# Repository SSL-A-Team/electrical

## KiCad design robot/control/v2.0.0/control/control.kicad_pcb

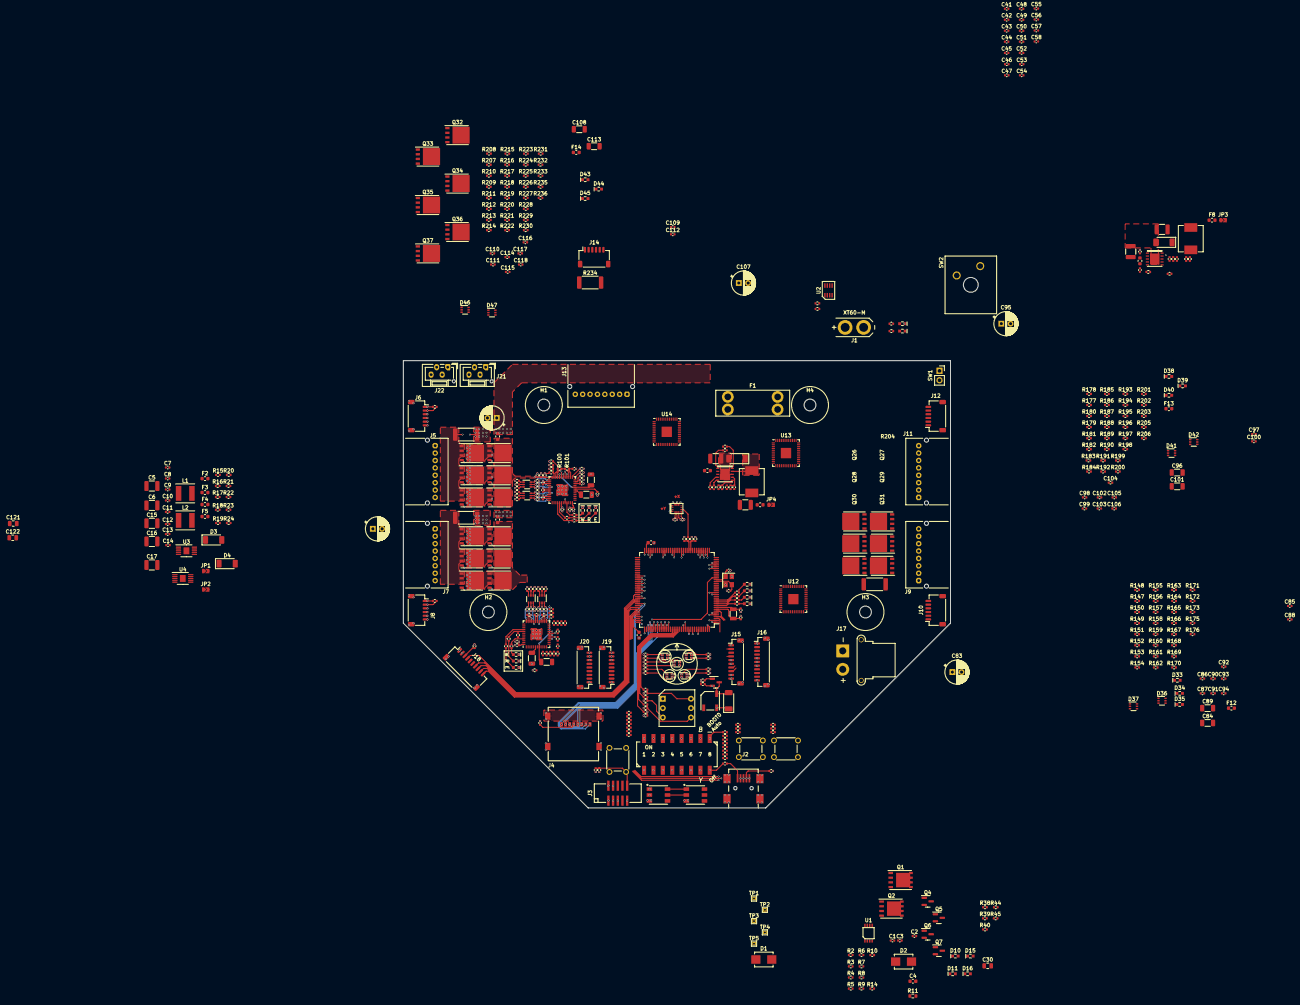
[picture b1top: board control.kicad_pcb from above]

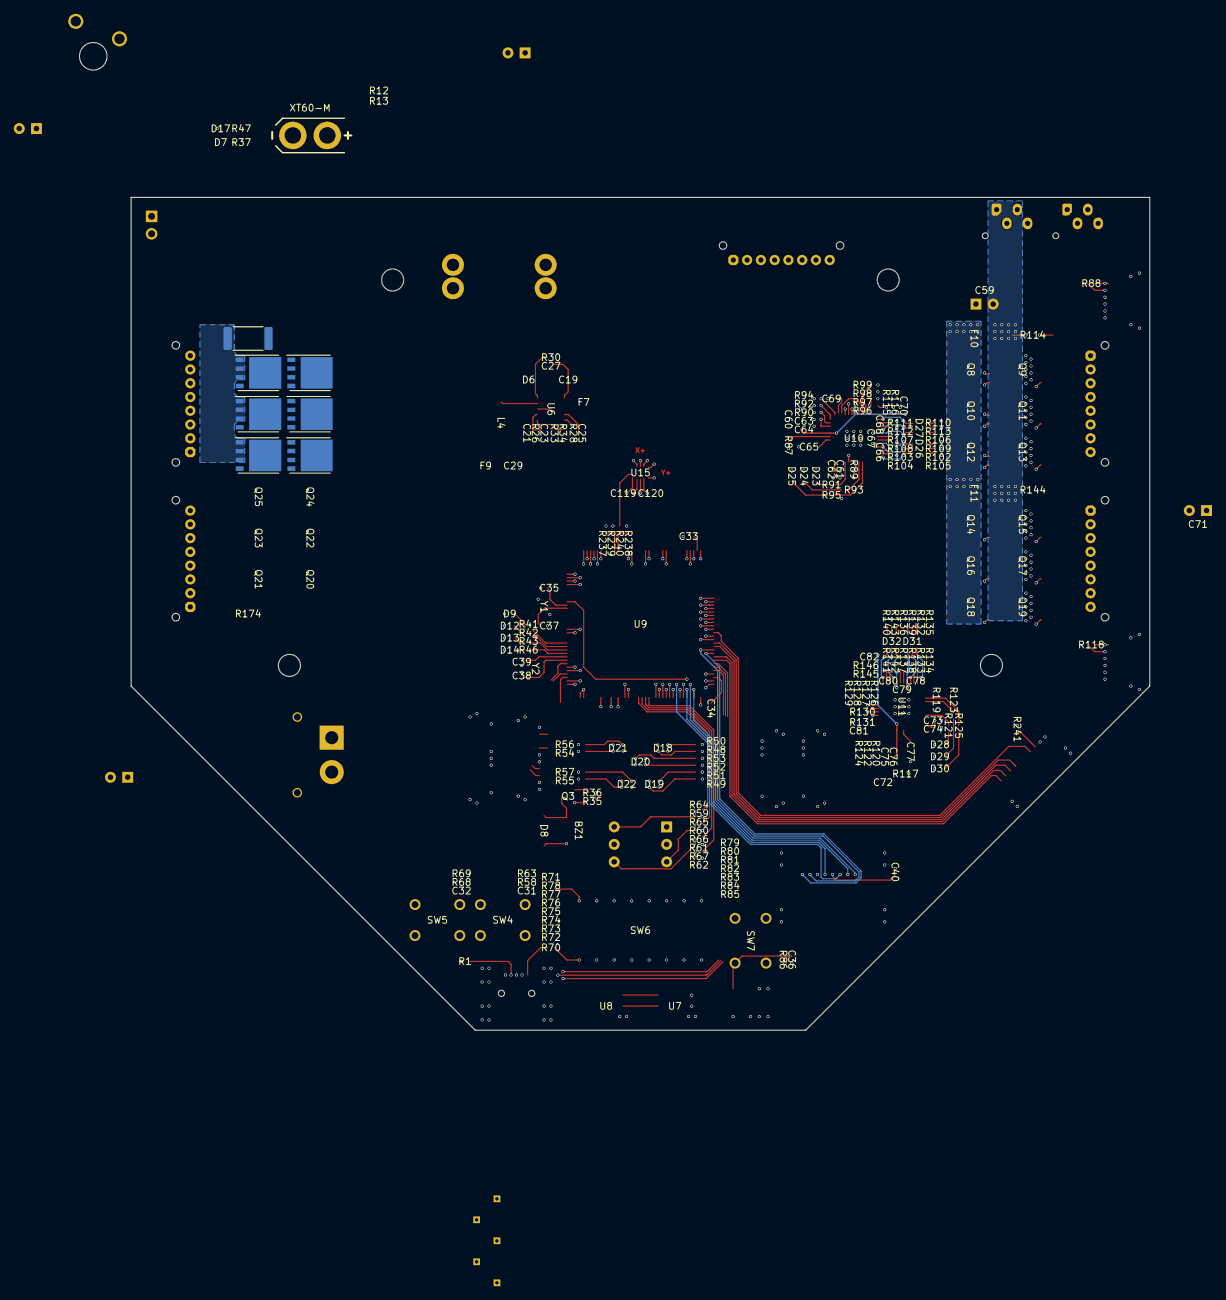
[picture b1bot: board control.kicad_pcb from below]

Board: 6 copper layers, 148.0 x 121.0 mm, 525 parts (7 on the bottom side), 435 nets.

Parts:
BZ1: MLT-5020
C1, C2, C3, C13, C14, C26, C27, C31, C32, C36, C40, C41, C42, C43, C44, C45, C46, C47, C48, C49, C50, C51, C53, C56, C57, C58, C62, C64, C66, C67, C68, C74, C76, C78, C79, C80, C86, C88, C90, C91, C92, C98, C100, C102, C103, C104, C110, C112, C114, C115, C116, C119, C120: 0.1uF 63V; C_0402_1005Metric
C4: 4700pF 63V; C_0603_1608Metric
C5, C6, C18, C19: 4.7uF 63V; C_1210_3225Metric
C7: 36pF; C_0402_1005Metric
C8: 24pF; C_0402_1005Metric
C9: 2700pF; C_0402_1005Metric
C10: 2200pF; C_0402_1005Metric
C11, C12: 10000pF; C_0402_1005Metric
C15, C16, C17: 100uF 10V; C_1210_3225Metric
C20, C21: 6.8pF; C_0402_1005Metric
C22, C23: 560pF; C_0402_1005Metric
C24, C25: 8200pF; C_0402_1005Metric
C28, C29: 47uF 25V; C_1210_3225Metric
C30, C121, C122: 4.7uF 25V; C_0805_2012Metric
C33, C34: 2.2uF 10V; C_0603_1608Metric
C35, C37: 11pF; C_0402_1005Metric
C38, C39: 8pF; C_0402_1005Metric
C52, C54, C55, C61, C63, C69, C70, C73, C75, C81, C82, C85, C87, C93, C94, C97, C99, C105, C106, C109, C111, C117, C118: 1uF 10V; C_0402_1005Metric
C59, C71, C83, C95, C107: 63ZLH47MEFC6.3X11; CP_Radial_D6.3mm_H11.0mm_P2.50mm
C60, C65, C72, C77, C84, C89, C96, C101, C108, C113: 1uF 63V; C_1206_3216Metric
D1, D2: 824521261; D_SMB_Non-Polar
D3, D4, D5, D6, D8: RBR5LAM60ATR; D_SOD-128
D7: XL-1608UWC-04; LED0603
D9, D12, D13, D14, D24, D29, D34, D39, D44: XL-1608UGC-04; LED0603
D10, D11, D15, D16, D25, D30, D35, D40, D45: XL-1608SURC-06; LED0603
D17, D23, D28, D33, D38, D43: XL-1608UOC-06; LED0603
D18, D19, D21, D22: LTST-C195KGJRKT; LED0606_S_1324
D20: MHT194YBCT; LED0606_Z_1324
D26, D27, D31, D32, D36, D37, D41, D42, D46, D47: BAS16VY; SOT-363_SC-70-6
F1: 15A; 3557-2
F2, F3, F4, F5, F6, F7: 0467002.NRHF; Fuse_0603_1608Metric
F8, F9: 0467004.NRHF; Fuse_0603_1608Metric
F10, F11, F12, F13, F14: 0467003.NRHF; Fuse_0603_1608Metric
H1, H2, H3, H4: M3; MountingHole_3.2mm_M3
J1: EC3-M; XT60-M_TH_WireMount
J2: 10033527-N3112MLF
J3: ARM_SWD; 3221-10-0300-00
J4: MEM2067-02-180-00-A
J5, J7, J9, J11, J13: S08B-PASK-2; JST_PA_S08B-PASK-2_1x08_P2.00mm_Horizontal
J6, J8, J10, J12, J14: SM06B-SRSS-TB; JST_SH_SM06B-SRSS-TB_1x06-1MP_P1.00mm_Horizontal
J15: BM10B-SRSS-TB; JST_SH_BM10B-SRSS-TB_1x10-1MP_P1.00mm_Vertical
J16: BM11B-SRSS-TB; JST_SH_BM11B-SRSS-TB_1x11-1MP_P1.00mm_Vertical
J17: XT30PW-F; AMASS_XT30PW-F_1x02_P2.50mm_Horizontal
J18: SM10B-SRSS-TB; JST_SH_SM10B-SRSS-TB_1x10-1MP_P1.00mm_Horizontal
J19, J20: BM09B-SRSS-TB; JST_SH_BM09B-SRSS-TB_1x09-1MP_P1.00mm_Vertical
J21, J22: B04B-ZESK-1D; JST_ZE_B04B-ZESK-1D_1x04_P1.50mm_Vertical
JP1: SB_{+3.3V}; SolderJumper-2_2.0x1.2mm_Closed
JP2: SB_{+5V}; SolderJumper-2_2.0x1.2mm_Closed
JP3: SB_{+12V}; SolderJumper-2_2.0x1.2mm_Closed
JP4: SB_{FAN}; SolderJumper-2_2.0x1.2mm_Closed
L1, L2: SDEI054T-100MS; SDEI054T
L3, L4: 0630CDMCCDS-4R7MC; 0630CDMCCDS
Q1, Q2: SQJA80EP-T1_GE3; PowerPAK_SO-8L_Single
Q3, Q4, Q5, Q6, Q7: BSS138K; SOT-23
Q8, Q9, Q10, Q11, Q12, Q13, Q14, Q15, Q16, Q17, Q18, Q19, Q20, Q21, Q22, Q23, Q24, Q25, Q26, Q27, Q28, Q29, Q30, Q31, Q32, Q33, Q34, Q35, Q36, Q37: STL90N10F7; PowerFLAT_5x6
R1, R12, R13, R14, R19, R20, R29, R30, R35, R38, R58, R59, R60, R61, R62, R68, R72, R73, R74, R75, R76, R77, R78, R86, R87, R88, R89, R90, R92, R94, R117, R118, R119, R120, R122, R124, R147, R148, R149, R150, R152, R154, R177, R178, R179, R180, R182, R184, R207, R208, R209, R210, R212, R214, R237, R238, R241: 4.7k; R_0402_1005Metric
R2, R7: 1k; R_0402_1005Metric
R3: 10M; R_0402_1005Metric
R4: 1.5M; R_0402_1005Metric
R5: 69.8k; R_0402_1005Metric
R6: 232k; R_0402_1005Metric
R8, R9, R36, R102, R105, R106, R109, R110, R113, R132, R135, R136, R139, R140, R143, R162, R165, R166, R169, R170, R173, R192, R195, R196, R199, R200, R203, R222, R225, R226, R229, R230, R233: 10; R_0402_1005Metric
R10: 100k; R_0402_1005Metric
R11: 5.1k; R_0603_1608Metric
R15: 18.7k; R_0402_1005Metric
R16, R37: 23.7k; R_0402_1005Metric
R17, R18: 162k; R_0402_1005Metric
R21: 30.9k; R_0402_1005Metric
R22, R24, R32, R34, R39, R40, R41, R42, R43, R44, R45, R46, R47, R48, R49, R50, R51, R52, R53, R54, R55, R56, R57, R70, R91, R93, R95, R99, R121, R123, R125, R129, R151, R153, R155, R159, R181, R183, R185, R189, R211, R213, R215, R219: 10k; R_0402_1005Metric
R23: 52.3k; R_0402_1005Metric
R25, R26: 56.2k; R_0402_1005Metric
R27, R28: 61.9k; R_0402_1005Metric
R31, R33: 140k; R_0402_1005Metric
R63, R64, R65, R66, R67, R69, R79, R80, R81, R82, R83, R84, R85, R239, R240: 100; R_0402_1005Metric
R71: 16k; R_0402_1005Metric
R96, R115, R126, R145, R156, R175, R186, R205, R216, R235: 2.37k; R_0402_1005Metric
R97, R127, R157, R187, R217: 649k; R_0402_1005Metric
R98, R128, R158, R188, R218: 53.6k; R_0402_1005Metric
R100, R130, R160, R190, R220: 26.7k; R_0402_1005Metric
R101, R131, R161, R191, R221: 22; R_0402_1005Metric
R103, R104, R107, R108, R111, R112, R133, R134, R137, R138, R141, R142, R163, R164, R167, R168, R171, R172, R193, R194, R197, R198, R201, R202, R223, R224, R227, R228, R231, R232: 62; R_0402_1005Metric
R114, R144, R174, R204, R234: HoLLR2512-3W-62mR-1%; R_2512_6332Metric
R116, R146, R176, R206, R236: 143k; R_0402_1005Metric
SW1: HDR_2P; PinSocket_1x02_P2.54mm_Vertical
SW2: CPG151101D91; SW_Kailh_PG1511
SW3: 221ADC16
SW4, SW5, SW7: TS02-66-73-BK-160-SCR-D
SW6: 219-8MST
TP1: Main; TestPoint_THTPad_1.0x1.0mm_Drill0.5mm
TP2: +3.3V; TestPoint_THTPad_1.0x1.0mm_Drill0.5mm
TP3: +5V; TestPoint_THTPad_1.0x1.0mm_Drill0.5mm
TP4: +12V; TestPoint_THTPad_1.0x1.0mm_Drill0.5mm
TP5: +V_{FAN}; TestPoint_THTPad_1.0x1.0mm_Drill0.5mm
U1: LTC4367; MS8
U2: LTC2955-1; LTC2955-TS8
U3, U4: TPS54260DGQ; HVSSOP-10-1EP_3x3mm_P0.5mm_EP1.57x1.88mm
U5, U6: TPS54561DPR; DPR
U7, U8: SK9822
U9: STM32H723ZGT6; LQFP-144_20x20mm_P0.5mm
U10, U11, U12, U13, U14: STSPIN32F0B; QFN-48-1EP_7x7mm_P0.5mm_EP2.8x2.8mm
U15: BMI323
Y1: TAXM8M4RDBCCT2T; Crystal_SMD_3225-4Pin_3.2x2.5mm
Y2: QT3CD-32.768KEZC-T; Crystal_SMD_3215-2Pin_3.2x1.5mm

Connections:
+3.3V: BZ1.1 (-), C40.1, C41.1, C42.1, C43.1, C44.1, C45.1, C46.1, C47.1, C48.1, C49.1, C50.1, C51.1, C52.1, C53.1, C54.1, C55.1, C56.1, C57.1, C58.1, C61.1, C62.1, C63.1, C64.1, C73.1, C74.1, C75.1, C76.1, C85.1, C86.1, C87.1, C88.1, C97.1, C98.1, C99.1, C100.1, C109.1, C110.1, C111.1, C112.1, C119.1, C120.1, D8.1 (K), J3.1 (VTref), J4.4 (VDD), J5.1, J6.1, J7.1, J8.1, J9.1, J10.1, J11.1, J12.1, J13.1, J14.1, J15.9, J16.11, J18.2, J19.7, J20.7, JP1.2 (B), R1.1, R12.1, R13.1, R19.1, R20.1, R29.1, R30.1, R50.2, R51.2, R53.2, R56.2, R57.2, R58.2, R68.2, R86.1, R88.2, R90.1, R92.1, R94.1, R97.1, R116.1, R118.2, R120.1, R122.1, R124.1, R127.1, R146.1, R148.2, R150.1, R152.1, R154.1, R157.1, R176.1, R178.2, R180.1, R182.1, R184.1, R187.1, R206.1, R208.2, R210.1, R212.1, R214.1, R217.1, R236.1, R237.1, R238.1, R241.1, SW3.C, SW6.1, SW6.2, SW6.3, SW6.4, SW6.5, SW6.6, SW6.7, TP2.1, U9.6 (VBAT), U9.17 (VDD), U9.30 (VDD), U9.32 (VREF+), U9.33 (VDDA), U9.39 (VDD), U9.52 (VDD), U9.62 (VDD), U9.72 (VDD), U9.84 (VDD), U9.95 (VDD33USB), U9.108 (VDD), U9.121 (VDD), U9.131 (VDD), U9.143 (PDR_ON), U9.144 (VDD), U10.10 (VDDA), U10.48 (VDD), U11.10 (VDDA), U11.48 (VDD), U12.10 (VDDA), U12.48 (VDD), U13.10 (VDDA), U13.48 (VDD), U14.10 (VDDA), U14.48 (VDD), U15.5 (VDDIO), U15.8 (VDD)
+5V: C30.2, J15.10, J19.8, J20.8, JP2.2 (B), TP3.1, U7.4 (VCC), U8.4 (VCC)
+12V: J19.9, J20.9, JP3.2 (B), TP4.1
+V_{BATT(FUSED)}: D1.2 (A2), F1.2, Q1.5 (D), R2.2, R3.1
+V_{BATT(PROTECTED)}: C59.1, C71.1, C83.1, C95.1, C107.1, F2.2, F3.2, F6.2, F7.2, F10.1, F11.1, F12.1, F13.1, F14.1, J17.2, Q2.5 (D), R10.1, R14.1, R37.1, R39.1, R40.1, R44.1, R45.1, TP1.1, U1.7 (V_{OUT})
+V_{BATT(RAW)}: F1.1, J1.2
+V_{FAN}: C121.2, C122.2, J21.2, J22.2, JP4.2 (B), TP5.1
/AIRDRIBBLER.PWM1: J21.4, U9.50 (PF12)
/AIRDRIBBLER.PWM2: J22.4, U9.53 (PF13)
/EXTLOGIC.CK: J19.4, U9.79 (PD10)
/EXTLOGIC.NSS: J19.3, U9.80 (PD11)
/EXTLOGIC.RX: J19.5, U9.70 (PB11)
/EXTLOGIC.TX: J19.6, U9.69 (PB10)
/EXTLOGIC.~DET: J19.2, U9.68 (PE15)
/FLOW.BOOT0: J20.4, U9.58 (PE7)
/FLOW.RX: J20.5, U9.56 (PG0)
/FLOW.TX: J20.6, U9.57 (PG1)
/FLOW.~DET: J20.2, U9.60 (PE9)
/FLOW.~RST: J20.3, U9.59 (PE8)
/IMU.INT1: J16.4, R237.2, R239.2, U9.47 (PB1)
/IMU.INT2: J16.3, R238.2, R240.2, U9.48 (PB2)
/IMU.MISO: J16.6, U9.42 (PA6), U15.1 (SDO)
/IMU.MOSI: J16.7, U9.43 (PA7), U15.14 (SDx)
/IMU.SCK: J16.5, U9.41 (PA5), U15.13 (SCx)
/IMU.~DET: J16.2, U9.49 (PF11)
/IMU.~SS0: U9.40 (PA4), U15.12 (CSB)
/IMU.~SS1: J16.10, U9.44 (PC4)
/IMU.~SS2: J16.9, U9.45 (PC5)
/IMU.~SS3: J16.8, U9.46 (PB0)
/Indicators/BUZZER: R35.1, R36.1, U9.5 (PE6)
/Indicators/DOTSTAR.CLK: R38.1, U7.2 (CKI), U9.133 (PB3/SWO/JTDO)
/Indicators/DOTSTAR.DAT: U7.1 (SDI), U9.135 (PB5)
/Indicators/LED.0: R41.1, U9.13 (PF3)
/Indicators/LED.1: R42.1, U9.12 (PF2)
/Indicators/LED.2: R43.1, U9.11 (PF1)
/Indicators/LED.3: R46.1, U9.10 (PF0)
/Indicators/PGOOD_{+5V}: Q6.1 (G), R20.2, U4.6 (PWRGD), U5.3 (EN), U6.3 (EN)
/Indicators/PGOOD_{+12V}: Q5.1 (G), R29.2, U5.10 (PWRGD)
/Indicators/PGOOD_{FAN}: Q7.1 (G), R30.2, U6.10 (PWRGD)
/Indicators/ROBOTID_{DISP}.BL: D19.2 (A2), D19.3 (K1), U9.115 (PD1)
/Indicators/ROBOTID_{DISP}.BR: D22.2 (A2), D22.3 (K1), U9.117 (PD3)
/Indicators/ROBOTID_{DISP}.FL: D18.2 (A2), D18.3 (K1), U9.114 (PD0)
/Indicators/ROBOTID_{DISP}.FR: D21.2 (A2), D21.3 (K1), U9.118 (PD4)
/Indicators/ROBOTID_{DISP}.TeamBlue: D20.2 (A2), D20.3 (K1), U9.85 (PD14)
/Indicators/ShutdownInitiated: R47.1, U9.14 (PF4)
/KICKER.BOOT0: J18.9, U9.100 (PA8)
/KICKER.PWRON: J18.4, U9.93 (PG8)
/KICKER.RX: J18.8, U9.97 (PC7)
/KICKER.TX: J18.7, U9.96 (PC6)
/KICKER.~DET: J18.3, R241.2
/KICKER.~RST: J18.10, U9.101 (PA9)
/Load Switch/PGOOD_{VBATT}: R10.2, U1.6 (~FAULT), U3.3 (EN)
/Load Switch/~INT_{PWRBTN}: R12.2, U2.8 (~INT), U9.55 (PF15)
/Load Switch/~KILL_{PWR}: R13.2, U2.2 (~KILL), U9.54 (PF14)
/MCU/BOOT0: R71.2, SW6.9, U9.138 (BOOT0)
/MCU/DIP.1: R79.2, U9.92 (PG7)
/MCU/DIP.2: R80.2, U9.91 (PG6)
/MCU/DIP.3: R81.2, U9.90 (PG5)
/MCU/DIP.4: R82.2, U9.89 (PG4)
/MCU/DIP.5: R83.2, U9.88 (PG3)
/MCU/DIP.6: R84.2, U9.87 (PG2)
/MCU/ID_{SW}.IDX0: R67.2, U9.124 (PG9)
/MCU/ID_{SW}.IDX1: R66.2, U9.125 (PG10)
/MCU/ID_{SW}.IDX2: R65.2, U9.126 (PG11)
/MCU/ID_{SW}.IDX3: R64.2, U9.127 (PG12)
/MCU/IsBlueTeam: R85.2, U9.86 (PD15)
/MCU/MOTOR_{BL}.BOOT0: R119.1, U9.20 (PF8), U11.42 (BOOT0)
/MCU/MOTOR_{BL}.RX: U9.18 (PF6), U11.38 (PA14/SWDCLK/USART1_{TX}/BL_UART_{TX})
/MCU/MOTOR_{BL}.TX: U9.19 (PF7), U11.39 (PA15/USART1_{RX}/BL_UART_{RX})
/MCU/MOTOR_{BL}.~RST: R117.2, U9.21 (PF9), U11.7 (NRST)
/MCU/MOTOR_{BR}.BOOT0: R149.1, U9.140 (PB9), U12.42 (BOOT0)
/MCU/MOTOR_{BR}.RX: U9.141 (PE0), U12.38 (PA14/SWDCLK/USART1_{TX}/BL_UART_{TX})
/MCU/MOTOR_{BR}.TX: U9.142 (PE1), U12.39 (PA15/USART1_{RX}/BL_UART_{RX})
/MCU/MOTOR_{BR}.~RST: R147.2, U9.139 (PB8), U12.7 (NRST)
/MCU/MOTOR_{DRB}.BOOT0: R209.1, U9.82 (PD13), U14.42 (BOOT0)
/MCU/MOTOR_{DRB}.RX: U9.73 (PB12), U14.38 (PA14/SWDCLK/USART1_{TX}/BL_UART_{TX})
/MCU/MOTOR_{DRB}.TX: U9.74 (PB13), U14.39 (PA15/USART1_{RX}/BL_UART_{RX})
/MCU/MOTOR_{DRB}.~RST: R207.2, U9.81 (PD12), U14.7 (NRST)
/MCU/MOTOR_{FL}.BOOT0: R89.1, U9.27 (PC1), U10.42 (BOOT0)
/MCU/MOTOR_{FL}.RX: U9.35 (PA1), U10.38 (PA14/SWDCLK/USART1_{TX}/BL_UART_{TX})
/MCU/MOTOR_{FL}.TX: U9.34 (PA0), U10.39 (PA15/USART1_{RX}/BL_UART_{RX})
/MCU/MOTOR_{FL}.~RST: R87.2, U9.26 (PC0), U10.7 (NRST)
/MCU/MOTOR_{FR}.BOOT0: R179.1, U9.77 (PD8), U13.42 (BOOT0)
/MCU/MOTOR_{FR}.RX: U9.76 (PB15), U13.38 (PA14/SWDCLK/USART1_{TX}/BL_UART_{TX})
/MCU/MOTOR_{FR}.TX: U9.75 (PB14), U13.39 (PA15/USART1_{RX}/BL_UART_{RX})
/MCU/MOTOR_{FR}.~RST: R177.2, U9.78 (PD9), U13.7 (NRST)
/MCU/SDMMC.CK: J4.5 (CLK), U9.113 (PC12)
/MCU/SDMMC.CMD: J4.3 (CMD), U9.116 (PD2)
/MCU/SDMMC.D0: J4.7 (DAT0), U9.98 (PC8)
/MCU/SDMMC.D1: J4.8 (DAT1), U9.99 (PC9)
/MCU/SDMMC.D2: J4.1 (DAT2), U9.111 (PC10)
/MCU/SDMMC.D3: J4.2 (CD/DAT3), U9.112 (PC11)
/MCU/SWCLK: J3.4 (SWDCLK/TCK), U9.109 (PA14/SWCLK/JTCK)
/MCU/SWDIO: J3.2 (SWDIO/TMS), U9.105 (PA13/SWDIO/JTMS)
/MCU/~BTN0: R63.2, U9.119 (PD5)
/MCU/~BTN1: R69.2, U9.122 (PD6)
/MCU/~RST: C36.1, J3.10 (~RESET), R86.2, SW7.2, U9.25 (NRST)
/Motors/MotorBL/ENCODER_{A}: J8.3, U11.17 (PA6/T3C1/T16C1/ADC6)
/Motors/MotorBL/ENCODER_{B}: J8.4, U11.18 (PA7/T3C2/T14C1/T17C1/ADC7)
/Motors/MotorBL/ENCODER_{Z}: J8.5, U11.19 (PB1/T3C4/T14C1/ADC9)
/Motors/MotorBL/ENCODER_{~DET}: J8.2, R118.1, U11.16 (PA5/ADC5)
/Motors/MotorBL/HALL_{1}: J7.3, R120.2, U11.11 (PA0/T2C1/ADC0/USART1_{CTS})
/Motors/MotorBL/HALL_{2}: J7.4, R122.2, U11.12 (PA1/T2C2/ADC1/USART1_{RTS})
/Motors/MotorBL/HALL_{3}: J7.2, R124.2, U11.13 (PA2/T2C3/ADC2/USART1_{TX})
/Motors/MotorBL/I_{SENSE(AMPLIFIED)}: R130.2, R131.1, U11.15 (PA4/T14C1/ADC4/USART1_{CK}), U11.21 (OP1O)
/Motors/MotorBL/I_{SENSE(FILTERED)}: C81.1, R131.2, U11.14 (PA3/T2C4/ADC3/USART1_{RX})
/Motors/MotorBL/I_{SENSE(RAW)}: Q15.1 (S), Q15.2 (S), Q15.3 (S), Q17.1 (S), Q17.2 (S), Q17.3 (S), Q19.1 (S), Q19.2 (S), Q19.3 (S), R126.1, R144.1, R145.1
/Motors/MotorBL/LED_{ERROR}: R125.1, U11.40 (PB6/USART1_{TX})
/Motors/MotorBL/LED_{FW_READY}: R123.1, U11.41 (PB7/USART1_{RX})
/Motors/MotorBL/LED_{WARN}: R121.1, U11.45 (PB8/T16C1)
/Motors/MotorBL/MOTOR_{U}: C78.2, J7.8, Q18.1 (S), Q18.2 (S), Q18.3 (S), Q19.5 (D), U11.34 (OUTU)
/Motors/MotorBL/MOTOR_{V}: C79.2, J7.7, Q16.1 (S), Q16.2 (S), Q16.3 (S), Q17.5 (D), U11.30 (OUTV)
/Motors/MotorBL/MOTOR_{W}: C80.2, J7.6, Q14.1 (S), Q14.2 (S), Q14.3 (S), Q15.5 (D), U11.26 (OUTW)
/Motors/MotorBL/V_{MOTOR}: C72.1, F11.2, Q14.5 (D), Q16.5 (D), Q18.5 (D), U11.8 (VM)
/Motors/MotorBR/ENCODER_{A}: J10.3, U12.17 (PA6/T3C1/T16C1/ADC6)
/Motors/MotorBR/ENCODER_{B}: J10.4, U12.18 (PA7/T3C2/T14C1/T17C1/ADC7)
/Motors/MotorBR/ENCODER_{Z}: J10.5, U12.19 (PB1/T3C4/T14C1/ADC9)
/Motors/MotorBR/ENCODER_{~DET}: J10.2, R148.1, U12.16 (PA5/ADC5)
/Motors/MotorBR/HALL_{1}: J9.3, R150.2, U12.11 (PA0/T2C1/ADC0/USART1_{CTS})
/Motors/MotorBR/HALL_{2}: J9.4, R152.2, U12.12 (PA1/T2C2/ADC1/USART1_{RTS})
/Motors/MotorBR/HALL_{3}: J9.2, R154.2, U12.13 (PA2/T2C3/ADC2/USART1_{TX})
/Motors/MotorBR/I_{SENSE(AMPLIFIED)}: R160.2, R161.1, U12.15 (PA4/T14C1/ADC4/USART1_{CK}), U12.21 (OP1O)
/Motors/MotorBR/I_{SENSE(FILTERED)}: C93.1, R161.2, U12.14 (PA3/T2C4/ADC3/USART1_{RX})
/Motors/MotorBR/I_{SENSE(RAW)}: Q21.1 (S), Q21.2 (S), Q21.3 (S), Q23.1 (S), Q23.2 (S), Q23.3 (S), Q25.1 (S), Q25.2 (S), Q25.3 (S), R156.1, R174.1, R175.1
/Motors/MotorBR/LED_{ERROR}: R155.1, U12.40 (PB6/USART1_{TX})
/Motors/MotorBR/LED_{FW_READY}: R153.1, U12.41 (PB7/USART1_{RX})
/Motors/MotorBR/LED_{WARN}: R151.1, U12.45 (PB8/T16C1)
/Motors/MotorBR/MOTOR_{U}: C90.2, J9.8, Q24.1 (S), Q24.2 (S), Q24.3 (S), Q25.5 (D), U12.34 (OUTU)
/Motors/MotorBR/MOTOR_{V}: C91.2, J9.7, Q22.1 (S), Q22.2 (S), Q22.3 (S), Q23.5 (D), U12.30 (OUTV)
/Motors/MotorBR/MOTOR_{W}: C92.2, J9.6, Q20.1 (S), Q20.2 (S), Q20.3 (S), Q21.5 (D), U12.26 (OUTW)
/Motors/MotorBR/V_{MOTOR}: C84.1, F12.2, Q20.5 (D), Q22.5 (D), Q24.5 (D), U12.8 (VM)
/Motors/MotorDRB/ENCODER_{A}: J14.3, U14.17 (PA6/T3C1/T16C1/ADC6)
/Motors/MotorDRB/ENCODER_{B}: J14.4, U14.18 (PA7/T3C2/T14C1/T17C1/ADC7)
/Motors/MotorDRB/ENCODER_{Z}: J14.5, U14.19 (PB1/T3C4/T14C1/ADC9)
/Motors/MotorDRB/ENCODER_{~DET}: J14.2, R208.1, U14.16 (PA5/ADC5)
/Motors/MotorDRB/HALL_{1}: J13.3, R210.2, U14.11 (PA0/T2C1/ADC0/USART1_{CTS})
/Motors/MotorDRB/HALL_{2}: J13.4, R212.2, U14.12 (PA1/T2C2/ADC1/USART1_{RTS})
/Motors/MotorDRB/HALL_{3}: J13.2, R214.2, U14.13 (PA2/T2C3/ADC2/USART1_{TX})
/Motors/MotorDRB/I_{SENSE(AMPLIFIED)}: R220.2, R221.1, U14.15 (PA4/T14C1/ADC4/USART1_{CK}), U14.21 (OP1O)
/Motors/MotorDRB/I_{SENSE(FILTERED)}: C117.1, R221.2, U14.14 (PA3/T2C4/ADC3/USART1_{RX})
/Motors/MotorDRB/I_{SENSE(RAW)}: Q33.1 (S), Q33.2 (S), Q33.3 (S), Q35.1 (S), Q35.2 (S), Q35.3 (S), Q37.1 (S), Q37.2 (S), Q37.3 (S), R216.1, R234.1, R235.1
/Motors/MotorDRB/LED_{ERROR}: R215.1, U14.40 (PB6/USART1_{TX})
/Motors/MotorDRB/LED_{FW_READY}: R213.1, U14.41 (PB7/USART1_{RX})
/Motors/MotorDRB/LED_{WARN}: R211.1, U14.45 (PB8/T16C1)
/Motors/MotorDRB/MOTOR_{U}: C114.2, J13.8, Q36.1 (S), Q36.2 (S), Q36.3 (S), Q37.5 (D), U14.34 (OUTU)
/Motors/MotorDRB/MOTOR_{V}: C115.2, J13.7, Q34.1 (S), Q34.2 (S), Q34.3 (S), Q35.5 (D), U14.30 (OUTV)
/Motors/MotorDRB/MOTOR_{W}: C116.2, J13.6, Q32.1 (S), Q32.2 (S), Q32.3 (S), Q33.5 (D), U14.26 (OUTW)
/Motors/MotorDRB/V_{MOTOR}: C108.1, F14.2, Q32.5 (D), Q34.5 (D), Q36.5 (D), U14.8 (VM)
/Motors/MotorFL/ENCODER_{A}: J6.3, U10.17 (PA6/T3C1/T16C1/ADC6)
/Motors/MotorFL/ENCODER_{B}: J6.4, U10.18 (PA7/T3C2/T14C1/T17C1/ADC7)
/Motors/MotorFL/ENCODER_{Z}: J6.5, U10.19 (PB1/T3C4/T14C1/ADC9)
/Motors/MotorFL/ENCODER_{~DET}: J6.2, R88.1, U10.16 (PA5/ADC5)
/Motors/MotorFL/HALL_{1}: J5.3, R90.2, U10.11 (PA0/T2C1/ADC0/USART1_{CTS})
/Motors/MotorFL/HALL_{2}: J5.4, R92.2, U10.12 (PA1/T2C2/ADC1/USART1_{RTS})
/Motors/MotorFL/HALL_{3}: J5.2, R94.2, U10.13 (PA2/T2C3/ADC2/USART1_{TX})
/Motors/MotorFL/I_{SENSE(AMPLIFIED)}: R100.2, R101.1, U10.15 (PA4/T14C1/ADC4/USART1_{CK}), U10.21 (OP1O)
/Motors/MotorFL/I_{SENSE(FILTERED)}: C69.1, R101.2, U10.14 (PA3/T2C4/ADC3/USART1_{RX})
/Motors/MotorFL/I_{SENSE(RAW)}: Q9.1 (S), Q9.2 (S), Q9.3 (S), Q11.1 (S), Q11.2 (S), Q11.3 (S), Q13.1 (S), Q13.2 (S), Q13.3 (S), R96.1, R114.1, R115.1
/Motors/MotorFL/LED_{ERROR}: R95.1, U10.40 (PB6/USART1_{TX})
/Motors/MotorFL/LED_{FW_READY}: R93.1, U10.41 (PB7/USART1_{RX})
/Motors/MotorFL/LED_{WARN}: R91.1, U10.45 (PB8/T16C1)
/Motors/MotorFL/MOTOR_{U}: C66.2, J5.8, Q12.1 (S), Q12.2 (S), Q12.3 (S), Q13.5 (D), U10.34 (OUTU)
/Motors/MotorFL/MOTOR_{V}: C67.2, J5.7, Q10.1 (S), Q10.2 (S), Q10.3 (S), Q11.5 (D), U10.30 (OUTV)
/Motors/MotorFL/MOTOR_{W}: C68.2, J5.6, Q8.1 (S), Q8.2 (S), Q8.3 (S), Q9.5 (D), U10.26 (OUTW)
/Motors/MotorFL/V_{MOTOR}: C60.1, F10.2, Q8.5 (D), Q10.5 (D), Q12.5 (D), U10.8 (VM)
/Motors/MotorFR/ENCODER_{A}: J12.3, U13.17 (PA6/T3C1/T16C1/ADC6)
/Motors/MotorFR/ENCODER_{B}: J12.4, U13.18 (PA7/T3C2/T14C1/T17C1/ADC7)
/Motors/MotorFR/ENCODER_{Z}: J12.5, U13.19 (PB1/T3C4/T14C1/ADC9)
/Motors/MotorFR/ENCODER_{~DET}: J12.2, R178.1, U13.16 (PA5/ADC5)
/Motors/MotorFR/HALL_{1}: J11.3, R180.2, U13.11 (PA0/T2C1/ADC0/USART1_{CTS})
/Motors/MotorFR/HALL_{2}: J11.4, R182.2, U13.12 (PA1/T2C2/ADC1/USART1_{RTS})
/Motors/MotorFR/HALL_{3}: J11.2, R184.2, U13.13 (PA2/T2C3/ADC2/USART1_{TX})
/Motors/MotorFR/I_{SENSE(AMPLIFIED)}: R190.2, R191.1, U13.15 (PA4/T14C1/ADC4/USART1_{CK}), U13.21 (OP1O)
/Motors/MotorFR/I_{SENSE(FILTERED)}: C105.1, R191.2, U13.14 (PA3/T2C4/ADC3/USART1_{RX})
/Motors/MotorFR/I_{SENSE(RAW)}: Q27.1 (S), Q27.2 (S), Q27.3 (S), Q29.1 (S), Q29.2 (S), Q29.3 (S), Q31.1 (S), Q31.2 (S), Q31.3 (S), R186.1, R204.1, R205.1
/Motors/MotorFR/LED_{ERROR}: R185.1, U13.40 (PB6/USART1_{TX})
/Motors/MotorFR/LED_{FW_READY}: R183.1, U13.41 (PB7/USART1_{RX})
/Motors/MotorFR/LED_{WARN}: R181.1, U13.45 (PB8/T16C1)
/Motors/MotorFR/MOTOR_{U}: C102.2, J11.8, Q30.1 (S), Q30.2 (S), Q30.3 (S), Q31.5 (D), U13.34 (OUTU)
/Motors/MotorFR/MOTOR_{V}: C103.2, J11.7, Q28.1 (S), Q28.2 (S), Q28.3 (S), Q29.5 (D), U13.30 (OUTV)
/Motors/MotorFR/MOTOR_{W}: C104.2, J11.6, Q26.1 (S), Q26.2 (S), Q26.3 (S), Q27.5 (D), U13.26 (OUTW)
/Motors/MotorFR/V_{MOTOR}: C96.1, F13.2, Q26.5 (D), Q28.5 (D), Q30.5 (D), U13.8 (VM)
/Power/Power Supply (Logic)/PGOOD_{+3.3V}: Q4.1 (G), R19.2, U3.6 (PWRGD), U4.3 (EN)
/RADIO.BOOT0: J15.7, U9.4 (PE5)
/RADIO.CTS: J15.4, U9.128 (PG13)
/RADIO.RTS: J15.3, U9.129 (PG14)
/RADIO.RX: J15.5, U9.1 (PE2)
/RADIO.TX: J15.6, U9.2 (PE3)
/RADIO.~DET: J15.2, U9.3 (PE4)
/RADIO.~RST: J15.8, U9.7 (PC13)
/USB_OTG.DM: J2.2 (D-), U9.103 (PA11)
/USB_OTG.DP: J2.3 (D+), U9.104 (PA12)
/USB_OTG.ID: J2.4 (ID), R1.2, U9.102 (PA10)
/USB_VBUS: J2.1 (VBUS), R70.2
GND: C1.2, C2.2, C3.2, C4.2, C5.2, C6.2, C7.2, C8.2, C9.2, C10.2, C11.2, C12.2, C15.2, C16.2, C17.2, C18.2, C19.2, C20.2, C21.2, C22.2, C23.2, C24.2, C25.2, C28.2, C29.2, C30.1, C31.2, C32.2, C33.2, C34.2, C35.2, C36.2, C37.2, C38.2, C39.2, C40.2, C41.2, C42.2, C43.2, C44.2, C45.2, C46.2, C47.2, C48.2, C49.2, C50.2, C51.2, C52.2, C53.2, C54.2, C55.2, C56.2, C57.2, C58.2, C59.2, C60.2, C61.2, C62.2, C63.2, C64.2, C65.2, C69.2, C70.2, C71.2, C72.2, C73.2, C74.2, C75.2, C76.2, C77.2, C81.2, C82.2, C83.2, C84.2, C85.2, C86.2, C87.2, C88.2, C89.2, C93.2, C94.2, C95.2, C96.2, C97.2, C98.2, C99.2, C100.2, C101.2, C105.2, C106.2, C107.2, C108.2, C109.2, C110.2, C111.2, C112.2, C113.2, C117.2, C118.2, C119.2, C120.2, C121.1, C122.1, D1.1 (A1), D2.1 (A1), D3.2 (A), D4.2 (A), D5.2 (A), D6.2 (A), D7.1 (K), D9.1 (K), D10.1 (K), D11.1 (K), D12.1 (K), D13.1 (K), D14.1 (K), D15.1 (K), D16.1 (K), D17.1 (K), D23.1 (K), D24.1 (K), D25.1 (K), D28.1 (K), D29.1 (K), D30.1 (K), D33.1 (K), D34.1 (K), D35.1 (K), D38.1 (K), D39.1 (K), D40.1 (K), D43.1 (K), D44.1 (K), D45.1 (K), J1.1, J2.5 (GND), J2.6 (Shield), J3.3 (GND), J3.5 (GND), J3.9 (GNDDetect), J4.6 (VSS), J4.9 (Anchor), J5.5, J6.6, J6.MP (MountPin), J7.5, J8.6, J8.MP (MountPin), J9.5, J10.6, J10.MP (MountPin), J11.5, J12.6, J12.MP (MountPin), J13.5, J14.6, J14.MP (MountPin), J15.1, J15.MP (MountPin), J16.1, J16.MP (MountPin), J17.1, J18.1, J18.MP (MountPin), J19.1, J19.MP (MountPin), J20.1, J20.MP (MountPin), J21.1, J22.1, Q3.2 (S), Q4.2 (S), Q5.2 (S), Q6.2 (S), Q7.2 (S), R6.1, R14.2, R17.2, R18.2, R22.2, R24.2, R27.2, R28.2, R32.2, R34.2, R35.2, R38.2, R48.1, R49.1, R52.1, R54.1, R55.1, R59.1, R60.1, R61.1, R62.1, R71.1, R72.1, R73.1, R74.1, R75.1, R76.1, R77.1, R78.1, R87.1, R89.2, R98.2, R99.1, R114.2, R117.1, R119.2, R128.2, R129.1, R144.2, R147.1, R149.2, R158.2, R159.1, R174.2, R177.1, R179.2, R188.2, R189.1, R204.2, R207.1, R209.2, R218.2, R219.1, R234.2, SW1.1, SW2.1, SW4.3, SW5.3, SW7.3, U1.4 (GND), U2.1 (ON), U2.4 (GND), U3.9 (GND), U3.11 (GND), U4.9 (GND), U4.11 (GND), U5.8 (GND), U5.TP (GND), U6.8 (GND), U6.TP (GND), U7.3 (GND), U8.3 (GND), U9.16 (VSS), U9.31 (VSSA), U9.38 (VSS), U9.51 (VSS), U9.61 (VSS), U9.83 (VSS), U9.94 (VSS), U9.107 (VSS), U9.120 (VSS), U9.130 (VSS), U10.20 (TESTMODE), U10.44 (GND), U10.49 (EPAD), U11.20 (TESTMODE), U11.44 (GND), U11.49 (EPAD), U12.20 (TESTMODE), U12.44 (GND), U12.49 (EPAD), U13.20 (TESTMODE), U13.44 (GND), U13.49 (EPAD), U14.20 (TESTMODE), U14.44 (GND), U14.49 (EPAD), U15.6 (GNDIO), U15.7 (GND), Y1.2, Y1.4
unnamed: BZ1.2 (+), D8.2 (A), Q3.3 (D)
unnamed: C4.1, R11.2
unnamed: C9.1, R15.2
unnamed: C10.1, R16.2
unnamed: C15.1, C17.1, F4.1, L1.2, R21.1
unnamed: C16.1, F5.1, L2.2, R23.1
unnamed: C22.1, R25.2
unnamed: C23.1, R26.2
unnamed: C28.1, F8.1, L3.2, R31.1
unnamed: C29.1, F9.1, L4.2, R33.1
unnamed: C31.1, R58.1, SW4.1
unnamed: C32.1, R68.1, SW5.1
unnamed: C33.1, C34.1, U9.71 (VCAP), U9.106 (VCAP)
unnamed: C1.1, D2.2 (A2), R2.1, U1.1 (V_{IN}), U2.6 (V_{in})
unnamed: C13.2, D3.1 (K), L1.1, U3.10 (PH)
unnamed: C14.2, D4.1 (K), L2.1, U4.10 (PH)
unnamed: C26.2, D5.1 (K), L3.1, U5.9 (SW)
unnamed: C27.2, D6.1 (K), L4.1, U6.9 (SW)
unnamed: D7.2 (A), R37.2
unnamed: D9.2 (A), R41.2
unnamed: D10.2 (A), Q4.3 (D), R39.2
unnamed: D11.2 (A), Q5.3 (D), R40.2
unnamed: D12.2 (A), R42.2
unnamed: D13.2 (A), R43.2
unnamed: D14.2 (A), R46.2
unnamed: D15.2 (A), Q6.3 (D), R44.2
unnamed: D16.2 (A), Q7.3 (D), R45.2
unnamed: D17.2 (A), R47.2
unnamed: D18.1 (A1), R50.1
unnamed: D18.4 (K2), R48.2
unnamed: D19.1 (A1), R51.1
unnamed: D19.4 (K2), R49.2
unnamed: D20.1 (A1), R53.1
unnamed: D20.4 (K2), R52.2
unnamed: D21.1 (A1), R56.1
unnamed: D21.4 (K2), R54.2
unnamed: D22.1 (A1), R57.1
unnamed: D22.4 (K2), R55.2
unnamed: D23.2 (A), R91.2
unnamed: D24.2 (A), R93.2
unnamed: D25.2 (A), R95.2
unnamed: D26.1 (A), R109.1
unnamed: D26.6 (K), R108.1, U10.32 (LSV)
unnamed: D26.2 (A), R102.1
unnamed: D26.5 (K), R103.1, U10.33 (HSU)
unnamed: D26.3 (A), R105.1
unnamed: D26.4 (K), R104.1, U10.36 (LSU)
unnamed: D27.1 (A), R110.1
unnamed: D27.6 (K), R111.1, U10.25 (HSW)
unnamed: D27.2 (A), R113.1
unnamed: D27.5 (K), R112.1, U10.28 (LSW)
unnamed: D27.3 (A), R106.1
unnamed: D27.4 (K), R107.1, U10.29 (HSV)
unnamed: D28.2 (A), R121.2
unnamed: D29.2 (A), R123.2
unnamed: D30.2 (A), R125.2
unnamed: D31.1 (A), R139.1
unnamed: D31.6 (K), R138.1, U11.32 (LSV)
unnamed: D31.2 (A), R132.1
unnamed: D31.5 (K), R133.1, U11.33 (HSU)
unnamed: D31.3 (A), R135.1
unnamed: D31.4 (K), R134.1, U11.36 (LSU)
unnamed: D32.1 (A), R140.1
unnamed: D32.6 (K), R141.1, U11.25 (HSW)
unnamed: D32.2 (A), R143.1
unnamed: D32.5 (K), R142.1, U11.28 (LSW)
unnamed: D32.3 (A), R136.1
unnamed: D32.4 (K), R137.1, U11.29 (HSV)
unnamed: D33.2 (A), R151.2
unnamed: D34.2 (A), R153.2
unnamed: D35.2 (A), R155.2
unnamed: D36.1 (A), R169.1
unnamed: D36.6 (K), R168.1, U12.32 (LSV)
unnamed: D36.2 (A), R162.1
unnamed: D36.5 (K), R163.1, U12.33 (HSU)
unnamed: D36.3 (A), R165.1
unnamed: D36.4 (K), R164.1, U12.36 (LSU)
unnamed: D37.1 (A), R170.1
unnamed: D37.6 (K), R171.1, U12.25 (HSW)
unnamed: D37.2 (A), R173.1
unnamed: D37.5 (K), R172.1, U12.28 (LSW)
unnamed: D37.3 (A), R166.1
unnamed: D37.4 (K), R167.1, U12.29 (HSV)
unnamed: D38.2 (A), R181.2
unnamed: D39.2 (A), R183.2
unnamed: D40.2 (A), R185.2
unnamed: D41.1 (A), R199.1
unnamed: D41.6 (K), R198.1, U13.32 (LSV)
unnamed: D41.2 (A), R192.1
unnamed: D41.5 (K), R193.1, U13.33 (HSU)
unnamed: D41.3 (A), R195.1
unnamed: D41.4 (K), R194.1, U13.36 (LSU)
unnamed: D42.1 (A), R200.1
unnamed: D42.6 (K), R201.1, U13.25 (HSW)
unnamed: D42.2 (A), R203.1
unnamed: D42.5 (K), R202.1, U13.28 (LSW)
unnamed: D42.3 (A), R196.1
unnamed: D42.4 (K), R197.1, U13.29 (HSV)
unnamed: D43.2 (A), R211.2
unnamed: D44.2 (A), R213.2
unnamed: D45.2 (A), R215.2
unnamed: D46.1 (A), R229.1
unnamed: D46.6 (K), R228.1, U14.32 (LSV)
unnamed: D46.2 (A), R222.1
unnamed: D46.5 (K), R223.1, U14.33 (HSU)
unnamed: D46.3 (A), R225.1
unnamed: D46.4 (K), R224.1, U14.36 (LSU)
unnamed: D47.1 (A), R230.1
unnamed: D47.6 (K), R231.1, U14.25 (HSW)
unnamed: D47.2 (A), R233.1
unnamed: D47.5 (K), R232.1, U14.28 (LSW)
unnamed: D47.3 (A), R226.1
unnamed: D47.4 (K), R227.1, U14.29 (HSV)
unnamed: F4.2, JP1.1 (A)
unnamed: F5.2, JP2.1 (A)
unnamed: F8.2, JP3.1 (A)
unnamed: F9.2, JP4.1 (A)
unnamed: Q1.4 (G), R8.1
unnamed: Q1.1 (S), Q1.2 (S), Q1.3 (S), Q2.1 (S), Q2.2 (S), Q2.3 (S)
unnamed: Q2.4 (G), R9.2
unnamed: Q3.1 (G), R36.2
unnamed: Q8.4 (G), R110.2, R111.2
unnamed: Q9.4 (G), R112.2, R113.2
unnamed: Q10.4 (G), R106.2, R107.2
unnamed: Q11.4 (G), R108.2, R109.2
unnamed: Q12.4 (G), R102.2, R103.2
unnamed: Q13.4 (G), R104.2, R105.2
unnamed: Q14.4 (G), R140.2, R141.2
unnamed: Q15.4 (G), R142.2, R143.2
unnamed: Q16.4 (G), R136.2, R137.2
unnamed: Q17.4 (G), R138.2, R139.2
unnamed: Q18.4 (G), R132.2, R133.2
unnamed: Q19.4 (G), R134.2, R135.2
unnamed: Q20.4 (G), R170.2, R171.2
unnamed: Q21.4 (G), R172.2, R173.2
unnamed: Q22.4 (G), R166.2, R167.2
unnamed: Q23.4 (G), R168.2, R169.2
unnamed: Q24.4 (G), R162.2, R163.2
unnamed: Q25.4 (G), R164.2, R165.2
unnamed: Q26.4 (G), R200.2, R201.2
unnamed: Q27.4 (G), R202.2, R203.2
unnamed: Q28.4 (G), R196.2, R197.2
unnamed: Q29.4 (G), R198.2, R199.2
unnamed: Q30.4 (G), R192.2, R193.2
unnamed: Q31.4 (G), R194.2, R195.2
unnamed: Q32.4 (G), R230.2, R231.2
unnamed: Q33.4 (G), R232.2, R233.2
unnamed: Q34.4 (G), R226.2, R227.2
unnamed: Q35.4 (G), R228.2, R229.2
unnamed: Q36.4 (G), R222.2, R223.2
unnamed: Q37.4 (G), R224.2, R225.2
unnamed: R3.2, R4.1
unnamed: R7.2, SW1.2, SW2.2
unnamed: R62.2, R67.1, SW3.1
unnamed: R63.1, SW4.2
unnamed: R69.1, SW5.2
unnamed: R70.1, SW6.8
unnamed: R72.2, R79.1, SW6.16
unnamed: R73.2, R80.1, SW6.15
unnamed: R74.2, R81.1, SW6.14
unnamed: R75.2, R82.1, SW6.13
unnamed: R76.2, R83.1, SW6.12
unnamed: R77.2, R84.1, SW6.11
unnamed: R78.2, R85.1, SW6.10
unnamed: R61.2, R66.1, SW3.4 (2)
unnamed: R60.2, R65.1, SW3.3 (4)
unnamed: R59.2, R64.1, SW3.6 (8)
unnamed: R8.2, R9.1, R11.1, U1.8 (GATE)
unnamed: R5.2, R6.2, U1.3 (OV)
unnamed: R4.2, R5.1, U1.2 (UV)
unnamed: U1.5 (~SHDN), U2.7 (EN)
unnamed: C3.1, U2.3 (TMR)
unnamed: C2.1, R7.1, U2.5 (~PB)
unnamed: C13.1, U3.1 (BOOT)
unnamed: C7.1, R15.1, U3.8 (COMP)
unnamed: R17.1, U3.5 (RT/CLK)
unnamed: C11.1, U3.4 (SS/TR)
unnamed: C5.1, F2.1, U3.2 (VIN)
unnamed: R21.2, R22.1, U3.7 (VSENSE)
unnamed: C14.1, U4.1 (BOOT)
unnamed: C8.1, R16.1, U4.8 (COMP)
unnamed: R18.1, U4.5 (RT/CLK)
unnamed: C12.1, U4.4 (SS/TR)
unnamed: C6.1, F3.1, U4.2 (VIN)
unnamed: R23.2, R24.1, U4.7 (VSENSE)
unnamed: C26.1, U5.1 (BOOT)
unnamed: C20.1, R25.1, U5.7 (COMP)
unnamed: R31.2, R32.1, U5.6 (FB)
unnamed: R27.1, U5.5 (RT/CLK)
unnamed: C24.1, U5.4 (SS/TR)
unnamed: C18.1, F6.1, U5.2 (VIN)
unnamed: C27.1, U6.1 (BOOT)
unnamed: C21.1, R26.1, U6.7 (COMP)
unnamed: R33.2, R34.1, U6.6 (FB)
unnamed: R28.1, U6.5 (RT/CLK)
unnamed: C25.1, U6.4 (SS/TR)
unnamed: C19.1, F7.1, U6.2 (VIN)
unnamed: U7.5 (CKO), U8.2 (CKI)
unnamed: U7.6 (SDO), U8.1 (SDI)
unnamed: C37.1, U9.23 (PH0/OSC_IN), Y1.3
unnamed: C35.1, U9.24 (PH1/OSC_OUT), Y1.1
unnamed: C38.1, U9.8 (PC14/OSC32_IN), Y2.1
unnamed: C39.1, U9.9 (PC15/OSC32_OUT), Y2.2
unnamed: C65.1, U10.6 (VREG12)
unnamed: C66.1, U10.35 (VBOOTU)
unnamed: C67.1, U10.31 (VBOOTV)
unnamed: C68.1, U10.27 (VBOOTW)
unnamed: R99.2, R100.1, U10.22 (OP1N)
unnamed: R96.2, R97.2, R98.1, U10.23 (OP1P)
unnamed: C70.1, R115.2, R116.2, U10.24 (OC_COMP)
unnamed: C77.1, U11.6 (VREG12)
unnamed: C78.1, U11.35 (VBOOTU)
unnamed: C79.1, U11.31 (VBOOTV)
unnamed: C80.1, U11.27 (VBOOTW)
unnamed: R129.2, R130.1, U11.22 (OP1N)
unnamed: R126.2, R127.2, R128.1, U11.23 (OP1P)
unnamed: C82.1, R145.2, R146.2, U11.24 (OC_COMP)
unnamed: C89.1, U12.6 (VREG12)
unnamed: C90.1, U12.35 (VBOOTU)
unnamed: C91.1, U12.31 (VBOOTV)
unnamed: C92.1, U12.27 (VBOOTW)
unnamed: R159.2, R160.1, U12.22 (OP1N)
unnamed: R156.2, R157.2, R158.1, U12.23 (OP1P)
unnamed: C94.1, R175.2, R176.2, U12.24 (OC_COMP)
unnamed: C101.1, U13.6 (VREG12)
unnamed: C102.1, U13.35 (VBOOTU)
unnamed: C103.1, U13.31 (VBOOTV)
unnamed: C104.1, U13.27 (VBOOTW)
unnamed: R189.2, R190.1, U13.22 (OP1N)
unnamed: R186.2, R187.2, R188.1, U13.23 (OP1P)
unnamed: C106.1, R205.2, R206.2, U13.24 (OC_COMP)
unnamed: C113.1, U14.6 (VREG12)
unnamed: C114.1, U14.35 (VBOOTU)
unnamed: C115.1, U14.31 (VBOOTV)
unnamed: C116.1, U14.27 (VBOOTW)
unnamed: R219.2, R220.1, U14.22 (OP1N)
unnamed: R216.2, R217.2, R218.1, U14.23 (OP1P)
unnamed: C118.1, R235.2, R236.2, U14.24 (OC_COMP)
unnamed: R239.1, U15.4 (INT1)
unnamed: R240.1, U15.9 (INT2)

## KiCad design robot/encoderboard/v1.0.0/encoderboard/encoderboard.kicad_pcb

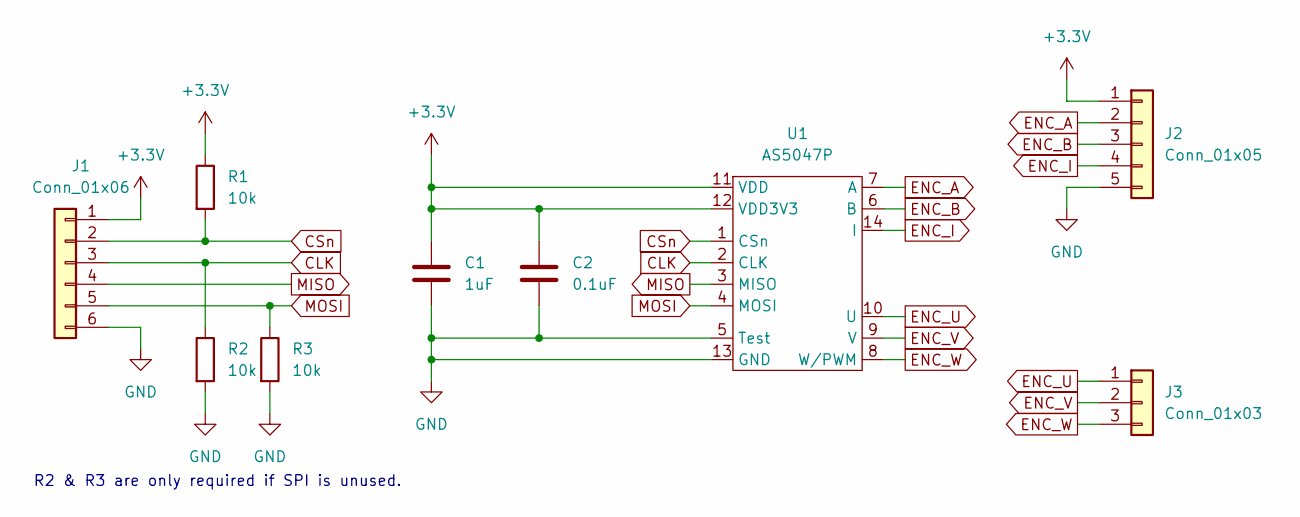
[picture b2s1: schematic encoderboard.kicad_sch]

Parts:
C1: 1uF; C_0402_1005Metric
C2: 0.1uF; C_0402_1005Metric
J1: Conn_01x06; WirePad_1x6_P1.27mm_L5.08mm
J2: Conn_01x05; WirePad_1x5_P1.27mm_L5.08mm
J3: Conn_01x03; PinHeader_1x03_P2.54mm_Vertical
R1, R2, R3: 10k; R_0402_1005Metric
U1: AS5047P; TSSOP-14_4.4x5mm_P0.65mm

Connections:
+3V3: C1.1, C2.1, J1.1, J2.1, R1.1, U1.11 (VDD), U1.12 (VDD3V3)
CLK: J1.3, R2.1, U1.2 (CLK)
CSn: J1.2, R1.2, U1.1 (CSn)
ENC_A: J2.2, U1.7 (A)
ENC_B: J2.3, U1.6 (B)
ENC_I: J2.4, U1.14 (I)
ENC_U: J3.1, U1.10 (U)
ENC_V: J3.2, U1.9 (V)
ENC_W: J3.3, U1.8 (W/PWM)
GND: C1.2, C2.2, J1.6, J2.5, R2.2, R3.2, U1.5 (Test), U1.13 (GND)
MISO: J1.4, U1.3 (MISO)
MOSI: J1.5, R3.1, U1.4 (MOSI)

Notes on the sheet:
R2 & R3 are only required if SPI is unused.

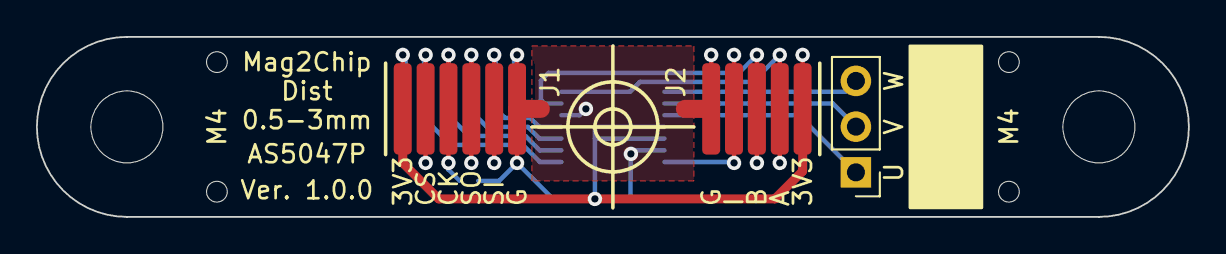
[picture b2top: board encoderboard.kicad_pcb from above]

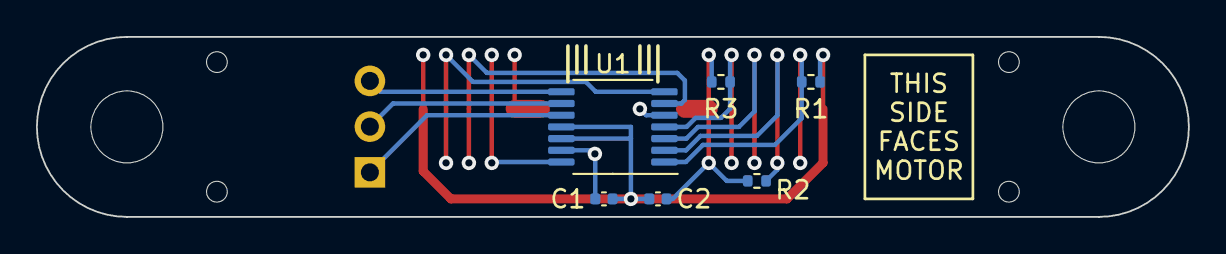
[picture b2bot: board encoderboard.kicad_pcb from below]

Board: 2 copper layers, 64.0 x 10.0 mm, 15 parts (6 on the bottom side), 12 nets.

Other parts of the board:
JLCTH1, JLCTH2, JLCTH3, JLCTH4: JLC_Tooling_Hole
MH1, MH2: MountingHole_4mm

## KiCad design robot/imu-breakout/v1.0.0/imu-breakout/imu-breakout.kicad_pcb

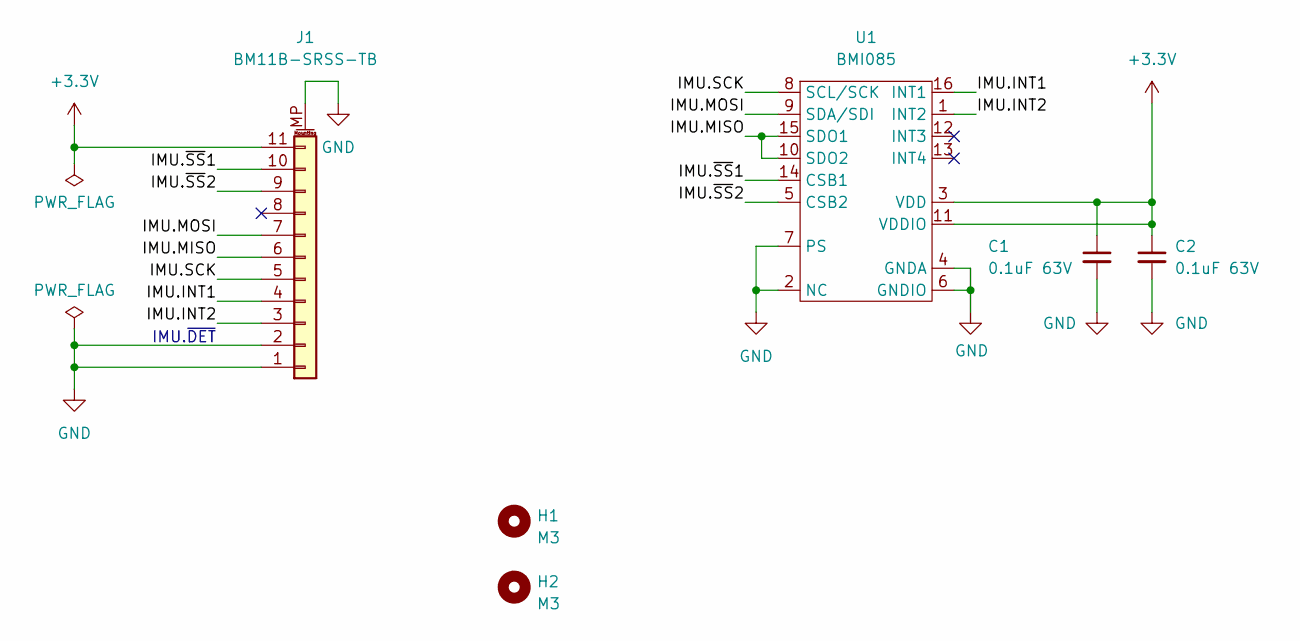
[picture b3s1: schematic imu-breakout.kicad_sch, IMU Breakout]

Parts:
C1, C2: 0.1uF 63V; C_0402_1005Metric
H1, H2: M3; MountingHole_3.2mm_M3
J1: BM11B-SRSS-TB; JST_SH_BM11B-SRSS-TB_1x11-1MP_P1.00mm_Vertical
U1: BMI085; LGA-16_3.0x4.5x0.95mm

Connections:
+3V3: C1.1, C2.1, J1.11, U1.3 (VDD), U1.11 (VDDIO)
/IMU.INT1: J1.4, U1.16 (INT1)
/IMU.INT2: J1.3, U1.1 (INT2)
/IMU.MISO: J1.6, U1.10 (SDO2), U1.15 (SDO1)
/IMU.MOSI: J1.7, U1.9 (SDA/SDI)
/IMU.SCK: J1.5, U1.8 (SCL/SCK)
/IMU.~SS1: J1.10, U1.14 (CSB1)
/IMU.~SS2: J1.9, U1.5 (CSB2)
GND: C1.2, C2.2, J1.1, J1.2, J1.MP (MountPin), U1.2 (NC), U1.4 (GNDA), U1.6 (GNDIO), U1.7 (PS)

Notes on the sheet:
IMU.~{DET}
